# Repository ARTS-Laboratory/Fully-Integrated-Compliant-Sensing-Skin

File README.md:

# Fully-Integrated-Compliant-Sensing-Skin-(FICSS)

Additive manufactured structural sensing sheet with integrated electronics 

## Hardware

<p align="center">
 <br> 

</p>

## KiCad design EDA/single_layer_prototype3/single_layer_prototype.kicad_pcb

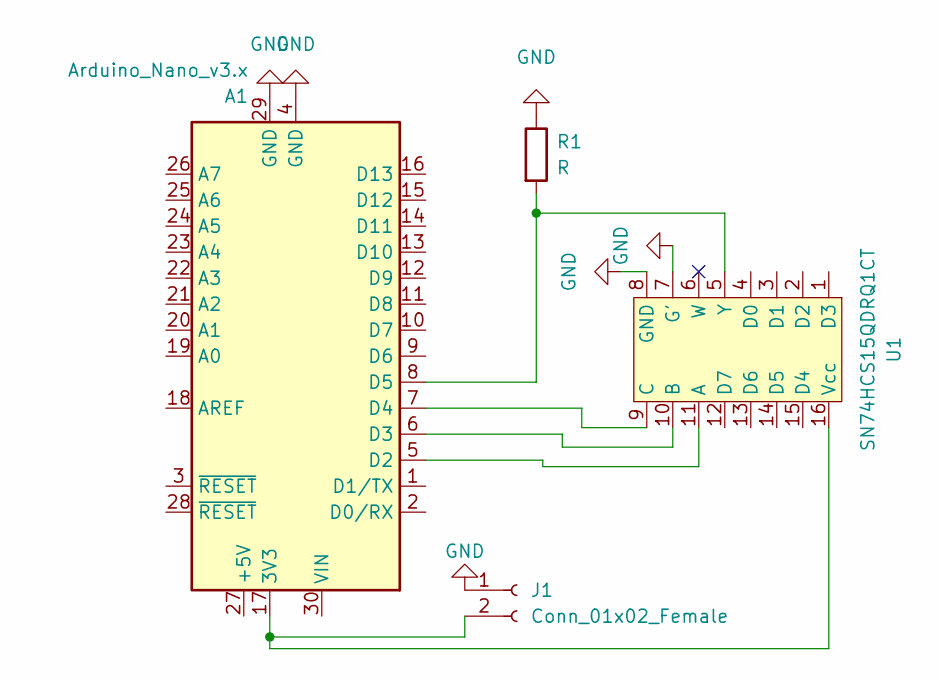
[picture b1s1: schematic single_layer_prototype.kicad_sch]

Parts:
A1: Arduino_Nano_v3.x; Arduino_Nano
J1: Conn_01x02_Female; banana_connector
R1: R; R_1206_3216Metric
U1: SN74HCS15QDRQ1CT; SOIC-16_3.9x9.9mm_P1.27mm

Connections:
GND: A1.4 (GND), A1.29 (GND), J1.1, R1.1, U1.7 (G'), U1.8 (GND)
unnamed: A1.5 (D2), U1.11 (A)
unnamed: A1.6 (D3), U1.10 (B)
unnamed: A1.7 (D4), U1.9 (C)
unnamed: A1.8 (D5), R1.2, U1.5 (Y)
unnamed: A1.17 (3V3), J1.2, U1.16 (Vcc)

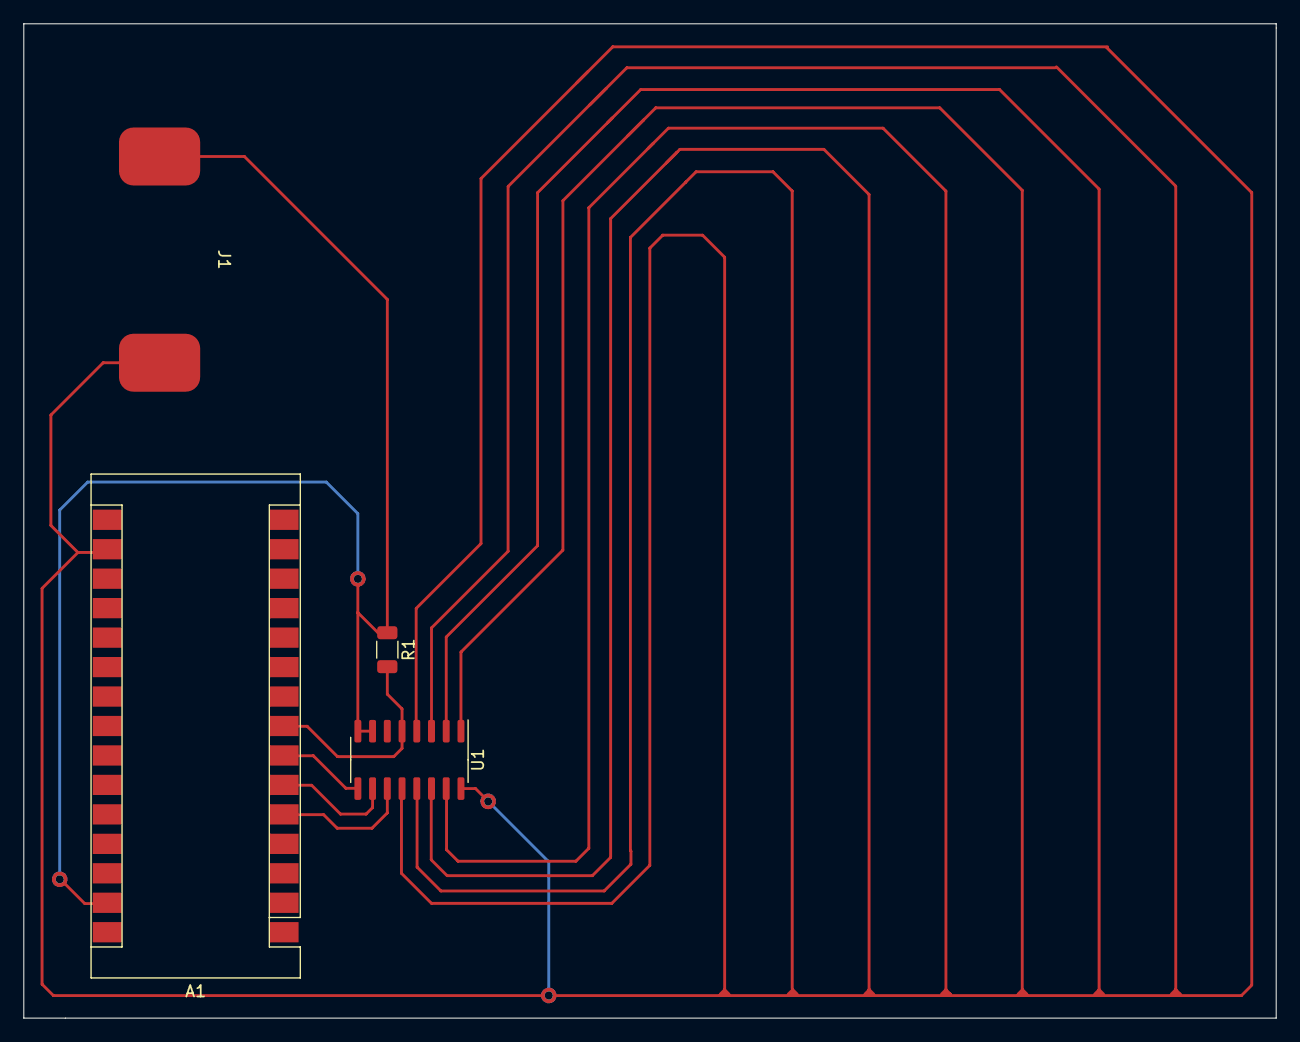
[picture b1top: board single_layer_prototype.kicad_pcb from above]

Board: 2 copper layers, 108.0 x 85.7 mm, 4 parts (0 on the bottom side), 6 nets.

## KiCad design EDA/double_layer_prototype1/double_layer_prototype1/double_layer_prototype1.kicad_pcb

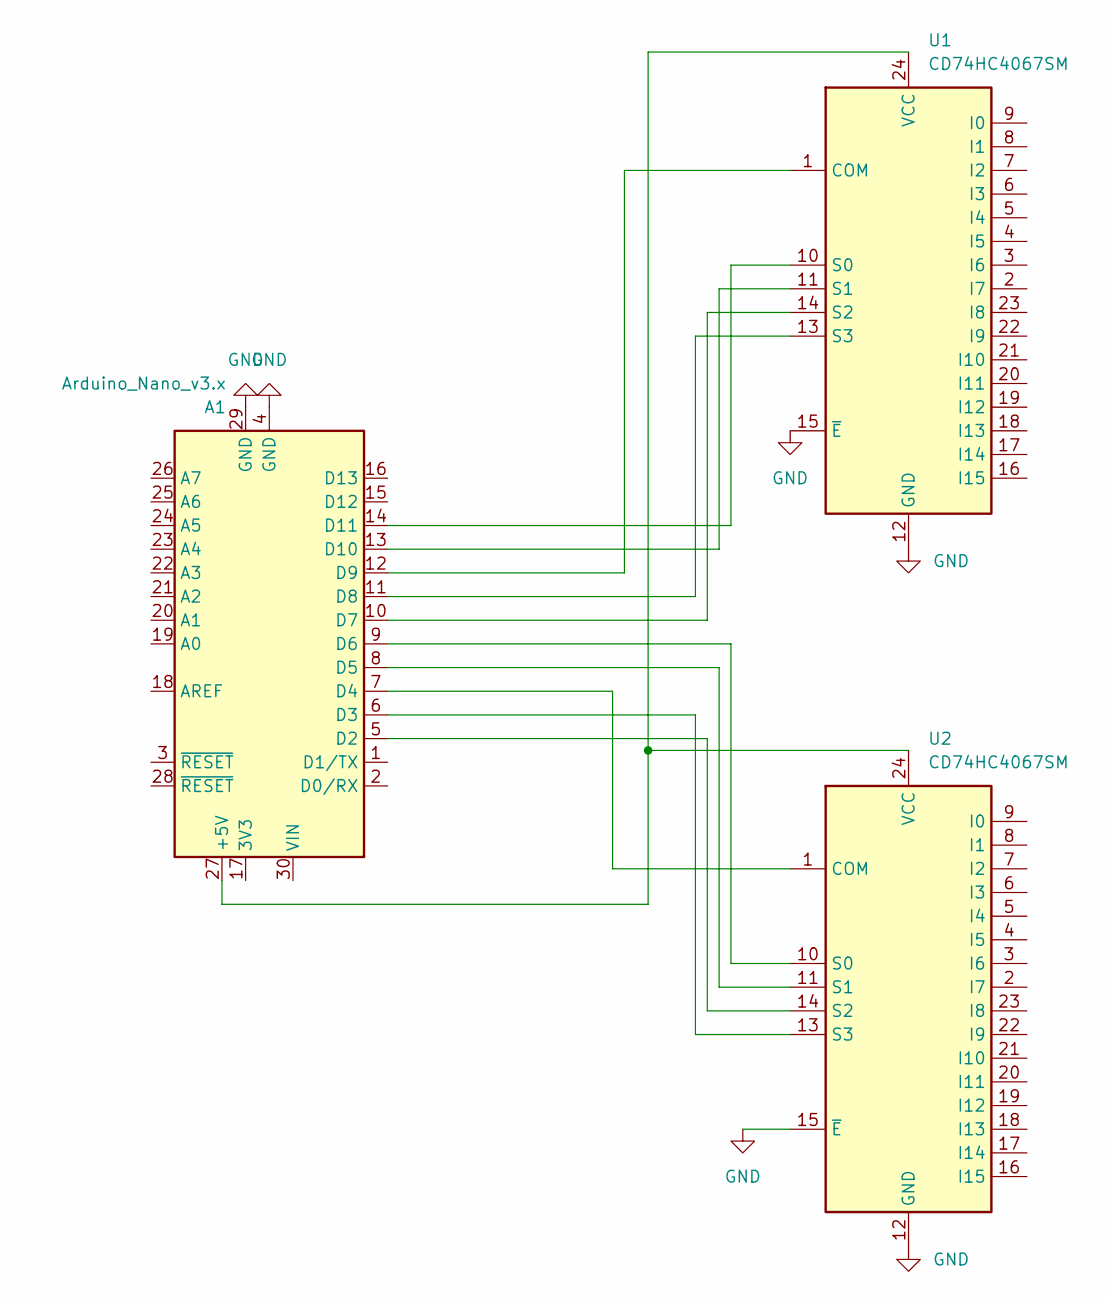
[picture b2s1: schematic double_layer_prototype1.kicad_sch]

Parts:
A1: Arduino_Nano_v3.x; Arduino_Nano
U1, U2: CD74HC4067SM; SSOP-24_5.3x8.2mm_P0.65mm

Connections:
GND: A1.4 (GND), A1.29 (GND), U1.12 (GND), U1.15 (~E), U2.12 (GND), U2.15 (~E)
unnamed: A1.7 (D4), U2.1 (COM)
unnamed: A1.27 (+5V), U1.24 (VCC), U2.24 (VCC)
unnamed: A1.12 (D9), U1.1 (COM)
unnamed: A1.14 (D11), U1.10 (S0)
unnamed: A1.13 (D10), U1.11 (S1)
unnamed: A1.11 (D8), U1.13 (S3)
unnamed: A1.10 (D7), U1.14 (S2)
unnamed: A1.9 (D6), U2.10 (S0)
unnamed: A1.8 (D5), U2.11 (S1)
unnamed: A1.6 (D3), U2.13 (S3)
unnamed: A1.5 (D2), U2.14 (S2)

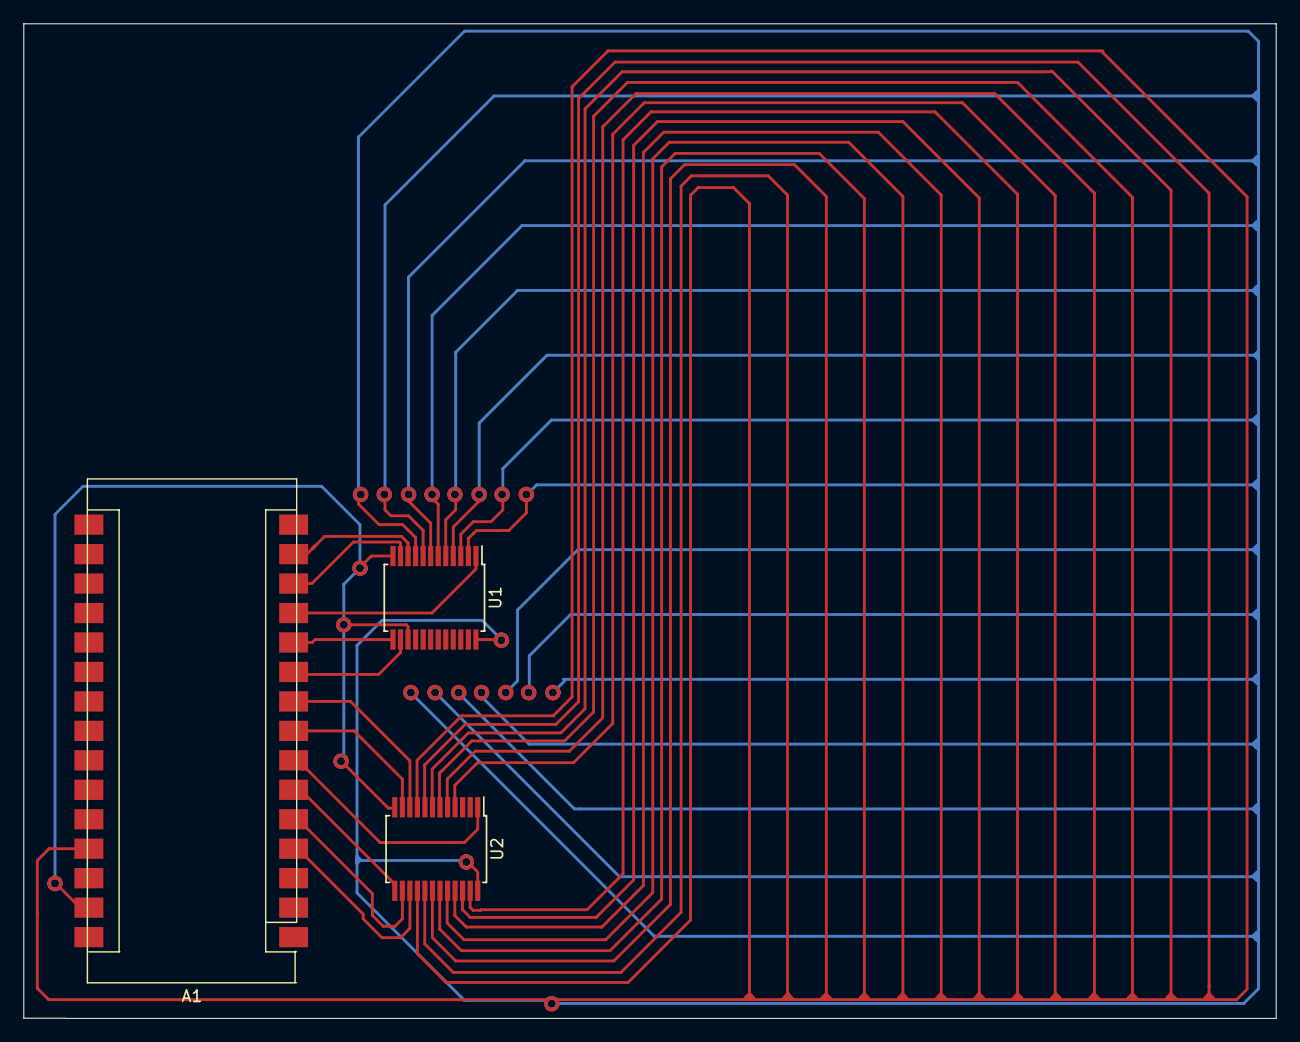
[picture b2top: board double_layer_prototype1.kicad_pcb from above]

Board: 2 copper layers, 108.0 x 85.8 mm, 3 parts (0 on the bottom side), 12 nets.

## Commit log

2022-05-16 added main figure
2022-05-19 create double layer lattice
2022-05-19 create single layer horizontal lines
2022-05-19 create single layer horizontal lines x2
2022-05-19 create single layer lattice
2022-05-23 add flare on trace connections to 5V rail
2022-09-02 add discrete resistive strain gauge
2022-09-02 update MTS test data
2022-09-02 add gerber
2022-10-28 add via template
2022-10-28 add via testing data
2022-10-28 add single layer prototype v1
2022-10-28 create gerber files
2022-10-28 create double layer grid
2022-10-28 duplicate EDA
2022-10-28 create double layer prototype v1
2022-11-23 create backups
2022-11-23 add libraries
2022-11-23 initial design
2022-11-23 update Arduino footprint
2022-11-23 add test data
2022-11-23 add symbol library
2023-05-09 add double layer prototype 1.2
2023-05-09 generate gerber files
2023-05-09 import ARTS Lab libraries
2023-05-09 create single layer prototype 3
2023-05-09 plot materials test data
2023-05-09 plot via resistance data
2023-05-09 plot wireless transfer test data
